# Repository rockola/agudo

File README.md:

# agudo
Phase 45

* v0.1: initial version, 1/8W resistors, SMD JFETs, verified
* v0.2: vibe switch, mostly SMD

## LICENSE

MIT License (see LICENSE.md)

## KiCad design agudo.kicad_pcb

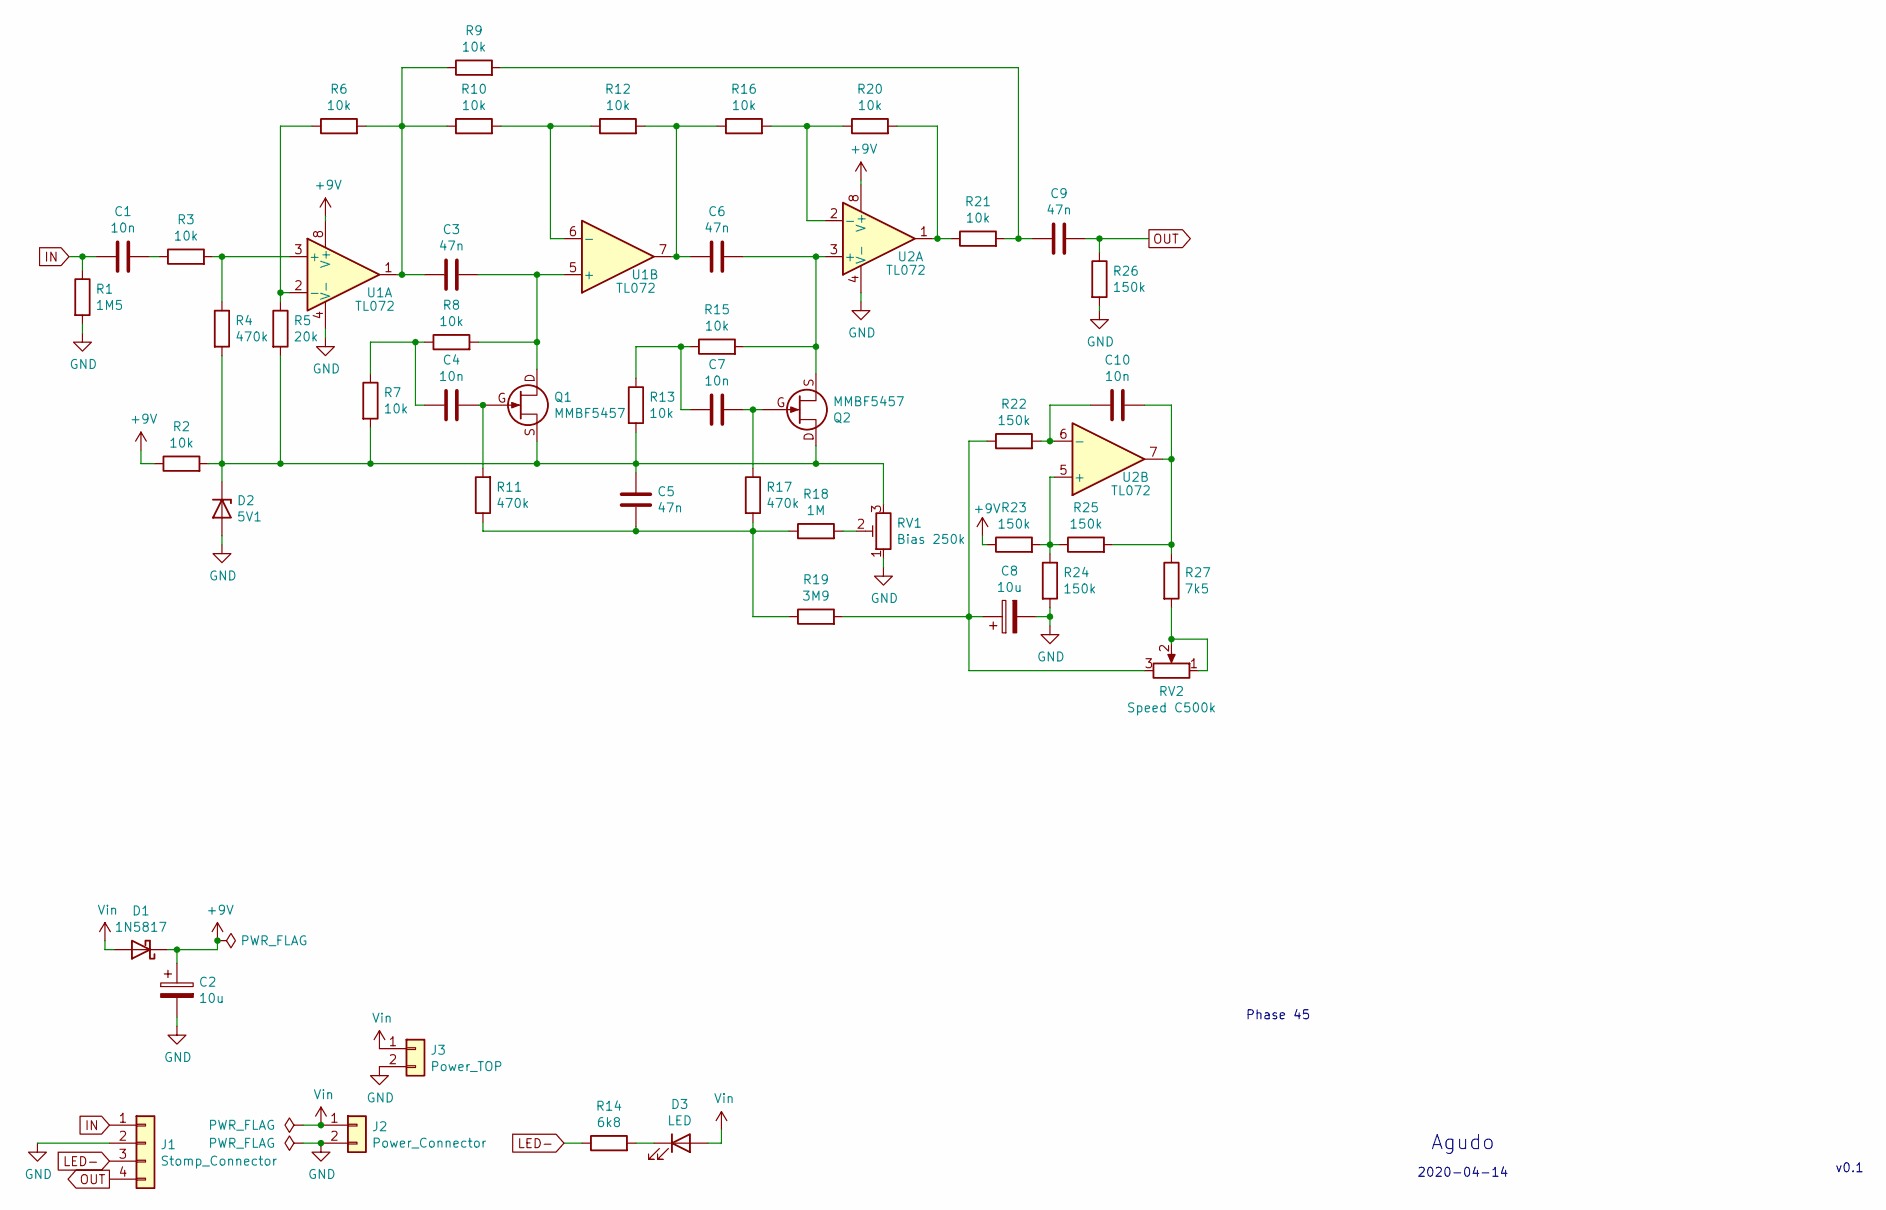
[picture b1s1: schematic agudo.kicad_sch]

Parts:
C1, C4, C7, C10: 10n; C_Box_7.2_2.5
C2, C8: 10u; CP_D5.0_P2.50
C3, C5, C6, C9: 47n; C_Box_7.2_2.5
D1: 1N5817; DO41-3
D2: 5V1; DO41-3
D3: LED; LED_D3.0mm
J1: Stomp_Connector; Stomp_4pin
J2: Power_Connector; Power_Header_2pin
J3: Power_TOP; Power_Header_2pin_TOP
Q1, Q2: MMBF5457; SOT-23_NJFET_DSG
R1: 1M5; R_0.125W_5mm
R2, R3, R6, R7, R8, R9, R10, R12, R13, R15, R16, R20, R21: 10k; R_0.125W_5mm
R4, R11, R17: 470k; R_0.125W_5mm
R5: 20k; R_0.125W_5mm
R14: 6k8; R_0.125W_5mm
R18: 1M; R_0.125W_5mm
R19: 3M9; R_0.125W_5mm
R22, R23, R24, R25, R26: 150k; R_0.125W_5mm
R27: 7k5; R_0.125W_5mm
RV1: Bias 250k; TRIM1
RV2: Speed C500k; 16mm_BoardMount
U1, U2: TL072; DIP-8_W7.62mm_Socket_LongPads

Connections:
+9V: C2.1, D1.1 (K), R2.1, R23.1, U1.8 (V+), U2.8 (V+)
GND: C2.2, C8.2, D2.2 (A), J1.2 (GND), J2.2 (GND), J3.2 (GND), R1.2, R24.2, R26.2, RV1.1, U1.4 (V-), U2.4 (V-)
IN: C1.1, J1.1 (IN), R1.1
LED-: J1.3 (SW), R14.1
unnamed: C1.2, R3.1
unnamed: C3.1, R6.2, R9.1, R10.1, U1.1
unnamed: C3.2, Q1.D, R8.2, U1.5 (+)
unnamed: C4.1, R7.1, R8.1
unnamed: C4.2, Q1.G, R11.2
unnamed: C5.1, D2.1 (K), Q1.S, Q2.D, R2.2, R4.2, R5.2, R7.2, R13.2, RV1.3
unnamed: C5.2, R11.1, R17.2, R18.1, R19.1
unnamed: C6.1, R12.2, R16.1, U1.7
unnamed: C6.2, Q2.S, R15.2, U2.3 (+)
unnamed: C7.1, R13.1, R15.1
unnamed: C7.2, Q2.G, R17.1
unnamed: C8.1, R19.2, R22.1, RV2.3
unnamed: C9.1, R9.2, R21.2
unnamed: C10.1, R22.2, U2.6 (-)
unnamed: C10.2, R25.2, R27.1, U2.7
unnamed: D3.1 (K), R14.2
unnamed: R3.2, R4.1, U1.3 (+)
unnamed: R5.1, R6.1, U1.2 (-)
unnamed: R10.2, R12.1, U1.6 (-)
unnamed: R16.2, R20.1, U2.2 (-)
unnamed: R18.2, RV1.2
unnamed: R20.2, R21.1, U2.1
unnamed: R23.2, R24.1, R25.1, U2.5 (+)
unnamed: R27.2, RV2.1, RV2.2
OUT: C9.2, J1.4 (OUT), R26.1
VIN: D1.2 (A), D3.2 (A), J2.1 (PWR), J3.1 (PWR)

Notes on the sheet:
Phase 45
Agudo
v0.1
2020-04-14

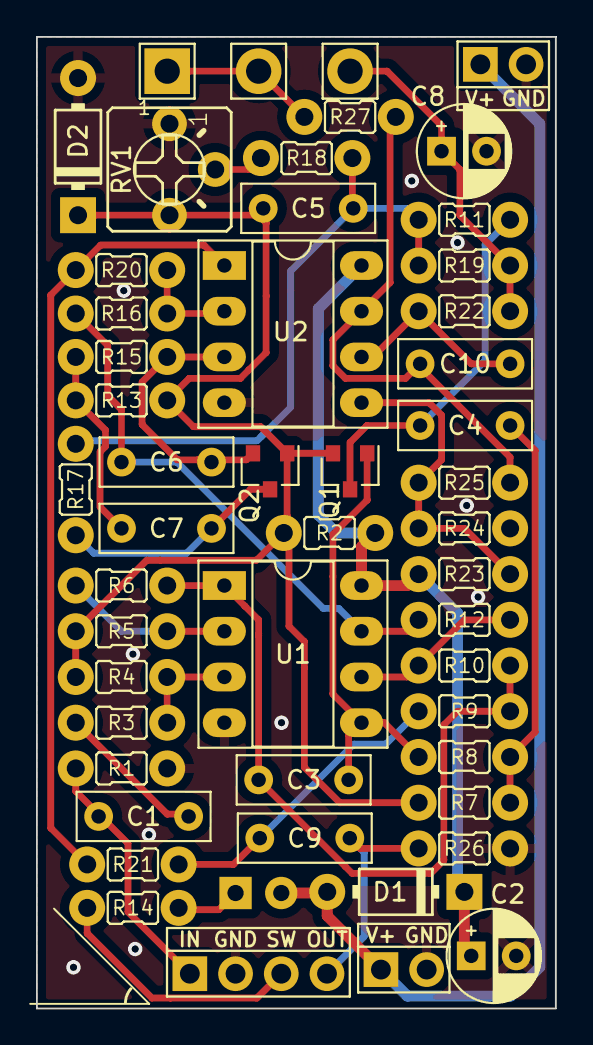
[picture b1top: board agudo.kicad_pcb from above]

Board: 2 copper layers, 28.8 x 54.0 mm, 49 parts (1 on the bottom side), 30 nets.

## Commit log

2020-04-28 initial
2020-04-29 slight silkscreen change; Gerbers sent to oshpark
2020-04-29 readme, license (MIT), preview images
2020-04-29 typo in image url
2020-04-29 some implementation details (SMD JFETs, etc.)
2020-04-29 board size note
2020-08-01 Update README.md
    Verification build succeeded 2020-07-31
2020-08-01 Update README.md
    v0.1 board not really 1590A compatible - board fits but jacks/stomp do not have enough space
2020-12-03 ignore backup dir
2020-12-03 v0.2 SMD Gerbers
2020-12-03 v0.2: SMD board, fully connected but bit of a spaghetti mess
2020-12-03 v0.2 schematic
2020-12-03 notes about v0.2 differences, new images
2020-12-03 v0.2 schem & project
2020-12-03 v0.2 Gerbers (with Protel filenames)
2020-12-03 Oshpark previews
2020-12-03 images now on branch smt
2022-01-11 updated to KiCad 6.0
